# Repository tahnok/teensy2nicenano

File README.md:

# Teensy2nicenano

Goal: make my original ergodox bluetooth capable by replacing the teensy 2.0 with a nice!nano v2

## Revision

### R1 

Errata:

 - The i2c pins (SDA and SCL) are swapped
 - The battery switch needs a solder jumper between pins 2 and 3

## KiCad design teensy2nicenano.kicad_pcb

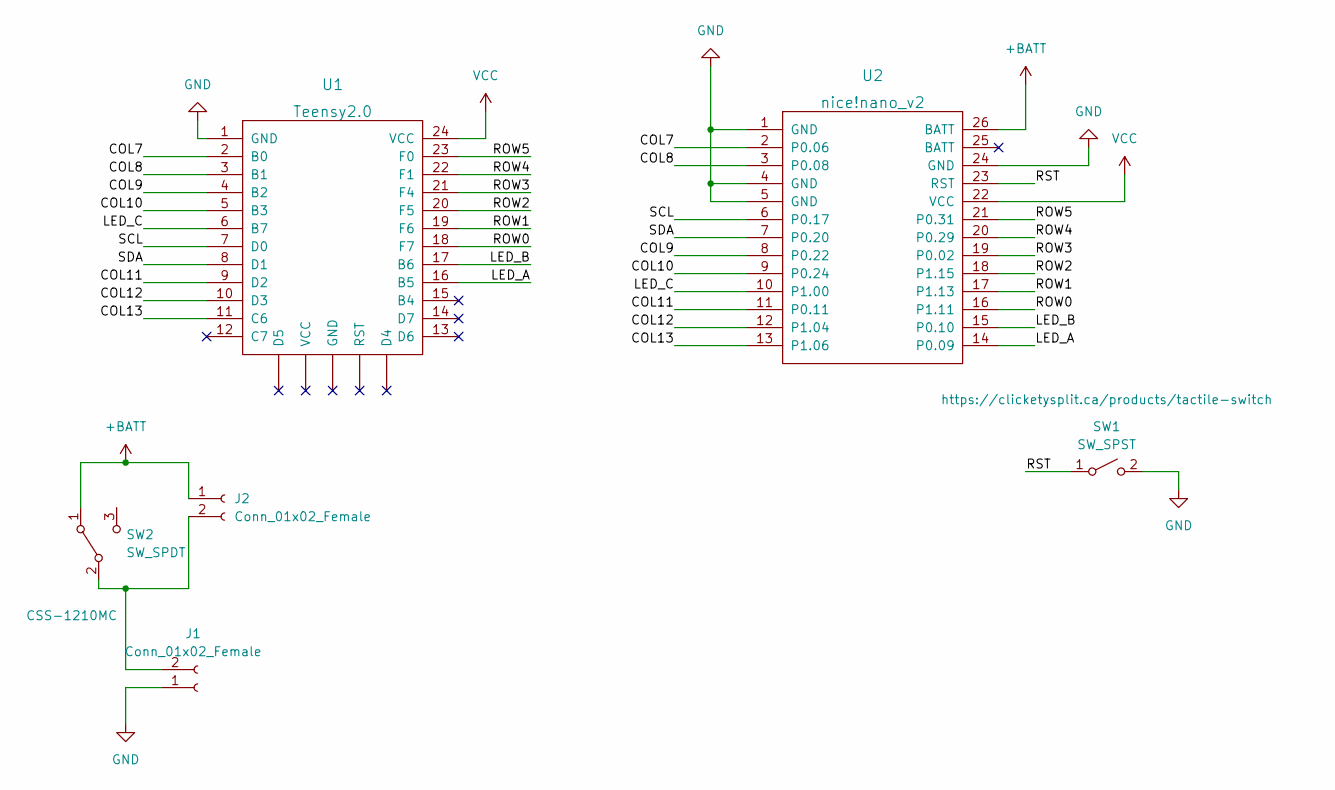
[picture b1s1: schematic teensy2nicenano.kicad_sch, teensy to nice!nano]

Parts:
J1: Conn_01x02_Female; PinHeader_2x1mm_P2mm_SMD_RA
J2: Conn_01x02_Female; PinHeader_1x02_P2.54mm_Vertical
SW1: SW_SPST; ResetSW
SW2: SW_SPDT; SPDT_right_angle; Digikey part CSS-1210MC
U1: Teensy2.0; Teensy2.0_trim
U2: nice!nano_v2; nice!nano v2

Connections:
+BATT: J2.1, SW2.1 (A), U2.26 (BATT)
/COL7: U1.2 (B0), U2.2 (P0.06)
/COL8: U1.3 (B1), U2.3 (P0.08)
/COL9: U1.4 (B2), U2.8 (P0.22)
/COL10: U1.5 (B3), U2.9 (P0.24)
/COL11: U1.9 (D2), U2.11 (P0.11)
/COL12: U1.10 (D3), U2.12 (P1.04)
/COL13: U1.11 (C6), U2.13 (P1.06)
/LED_A: U1.16 (B5), U2.14 (P0.09)
/LED_B: U1.17 (B6), U2.15 (P0.10)
/LED_C: U1.6 (B7), U2.10 (P1.00)
/ROW0: U1.18 (F7), U2.16 (P1.11)
/ROW1: U1.19 (F6), U2.17 (P1.13)
/ROW2: U1.20 (F5), U2.18 (P1.15)
/ROW3: U1.21 (F4), U2.19 (P0.02)
/ROW4: U1.22 (F1), U2.20 (P0.29)
/ROW5: U1.23 (F0), U2.21 (P0.31)
/RST: SW1.1 (A), U2.23 (RST)
/SCL: U1.7 (D0), U2.6 (P0.17)
/SDA: U1.8 (D1), U2.7 (P0.20)
GND: J1.1, SW1.2 (B), U1.1 (GND), U2.1 (GND), U2.4 (GND), U2.5 (GND), U2.24 (GND)
unnamed: J1.2, J2.2, SW2.2 (B)
VCC: U1.24 (VCC), U2.22 (VCC)

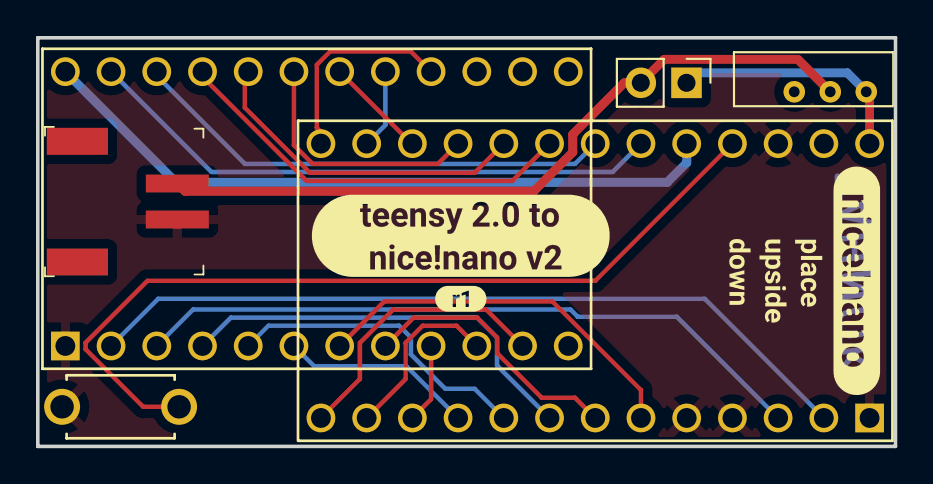
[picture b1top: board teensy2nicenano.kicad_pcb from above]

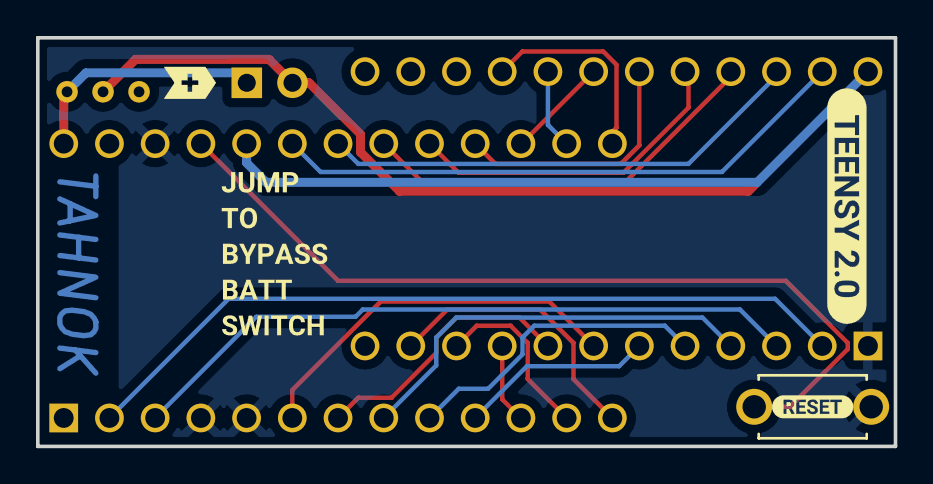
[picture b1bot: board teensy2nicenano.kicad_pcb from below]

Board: 2 copper layers, 47.7 x 22.7 mm, 14 parts (5 on the bottom side), 23 nets.

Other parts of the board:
kibuzzard-63CD6A48: G***; kibuzzard-63CD6A48
kibuzzard-63CD6B63: G***; kibuzzard-63CD6B63
kibuzzard-63CD8B85: G***; kibuzzard-63CD8B85
kibuzzard-63CD8F8E: G***; kibuzzard-63CD8F8E
kibuzzard-63CD60DD: G***; kibuzzard-63CD60DD
kibuzzard-63CD68E3: G***; kibuzzard-63CD68E3
kibuzzard-63CD68FE: G***; kibuzzard-63CD68FE
kibuzzard-63CD693F: G***; kibuzzard-63CD693F

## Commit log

2023-01-26 R1: initial version
2023-02-24 Update R1 errata
